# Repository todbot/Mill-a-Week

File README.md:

# Mill-a-Week
weekly experiments with othermachine Othermill by @todbot & @carlynorama

## Projects

### MyFirstOtherMillPendant - 22 May 2015
- Task: Use Illustrator to make a non-circuit design
- Notes:
  - Hard to align multiple SVGs

### LED-OtherCat - 29 May 2015
- Task: Make simple non-rectangular circuit in Eagle using 1/16" endmill
- Notes:
  - Can't do most through-hole with 1/16" --> Do extra hole pass at 1/32"

### HandCodedGerberPart01 - 5 Jun 2015
- Task: Explore how Otherplan imports Gerbers vs. SVGs, since in SVGs you can't do "put a hole here"
- Notes:
  - See [HandCodedGerberPart01/README.md](HandCodedGerberPart01/README.md)

### NeoJoints - 5 Jun 2015
- UPDATE: These have their own repo now: https://github.com/todbot/NeoJoints
- Task: Make "joints" for NeoPixel/WS2812 LED strip to make it easier to join pieces together
- Notes:
  - Programmatically generating these for different angles, LED spacing, etc. would be good.

### MillBug - 12 Jun 2015
- Task: Make an ATtiny85-based circuit using something other than LEDs
- Notes:
  - Soldering SMD on non-soldermask boards is a recipe for disaster if you have spazzy hands.
  - So, increase polygon "isolate" value for ground pour to give you
    bigger spacing to non-milled copper.

### OtherBlink - 3 Jul 2015 (originally Aug 2014)
- Task: See if Othermill can do SOIC & PLCC packages for ATtiny85 & WS2812, and make battery-powered flashing LED pendant with capsense touch sensor
- Notes:
  - capsense on battery-powered projects is challenging

### PlywoodPendant - 24 Jul 2015 
- Task: See if we can hit the independant plys in high-grade plywood
- Notes:
  - 
See if Othermill can do SOIC & PLCC packages for ATtiny85 & WS2812, and make battery-powered flashing LED pendant with capsense touch sensor
- Notes:
  - Lots of "chipout" around engraved areas. Would blue tape help?
  - We can make it thin enough for LEDs!

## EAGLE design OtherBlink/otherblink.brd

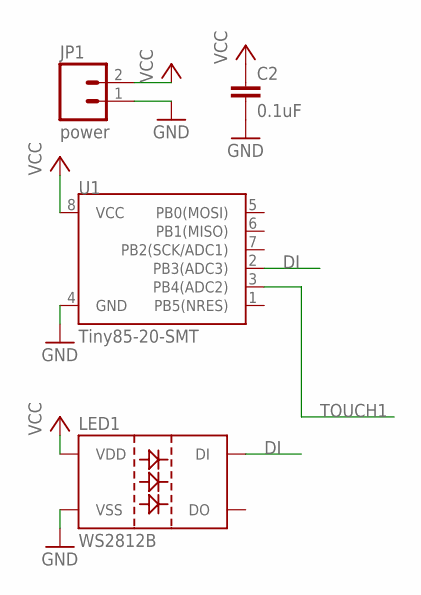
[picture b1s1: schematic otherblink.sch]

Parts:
C2: 0.1uF; 0603-CAP
JP1: power; 1X02_LONGPADS
LED1: WS2812B
U1: Tiny85-20-SMT; SO08-EIAJ

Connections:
DI: LED1.4 (DI), U1.2 (PB3(ADC3))
GND: C2.2, JP1.1, LED1.3 (VSS), U1.4 (GND)
TOUCH1: U1.3 (PB4(ADC2))
VCC: C2.1, JP1.2, LED1.1 (VDD), U1.8 (VCC)

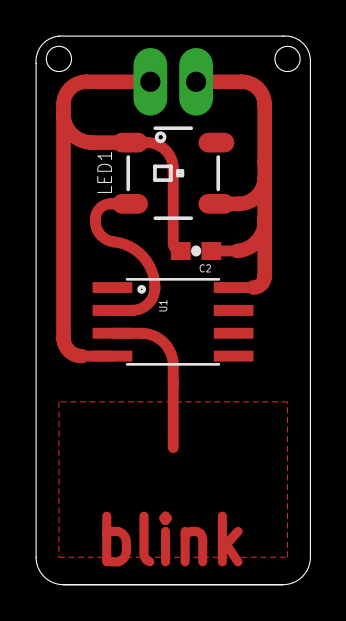
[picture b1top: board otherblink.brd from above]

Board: 2 copper layers, 15.2 x 30.5 mm, 4 parts (0 on the bottom side), 3 nets.

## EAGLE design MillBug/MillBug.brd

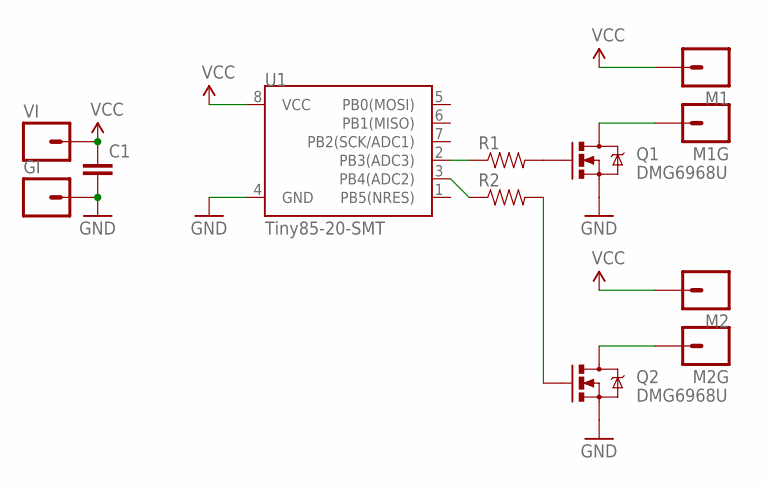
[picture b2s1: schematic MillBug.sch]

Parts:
C1: CAP0603-CAP; 0603-CAP
GI: M01PTH; 1X01
M1, M1G, M2, M2G: M01PTH; 1X01
Q1, Q2: DMG6968U; SOT23-3
R1, R2: RESISTOR0603-RES; 0603-RES
U1: Tiny85-20-SMT; SO08-EIAJ
VI: M01PTH; 1X01

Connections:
GND: C1.2, GI.1, Q1.2 (S), Q2.2 (S), U1.4 (GND)
unnamed: R2.1, U1.3 (PB4(ADC2))
unnamed: R1.1, U1.2 (PB3(ADC3))
unnamed: M1G.1, Q1.3 (D)
unnamed: Q1.1 (G), R1.2
unnamed: Q2.1 (G), R2.2
unnamed: M2G.1, Q2.3 (D)
VCC: C1.1, M1.1, M2.1, U1.8 (VCC), VI.1

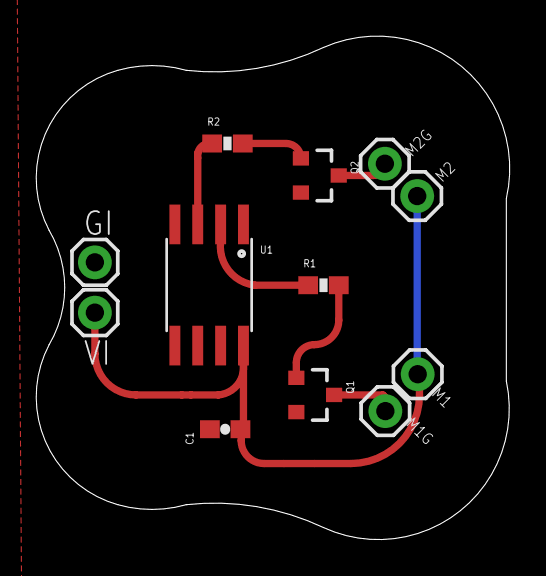
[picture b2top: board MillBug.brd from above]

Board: 2 copper layers, 26.3 x 28.0 mm, 12 parts (0 on the bottom side), 8 nets.

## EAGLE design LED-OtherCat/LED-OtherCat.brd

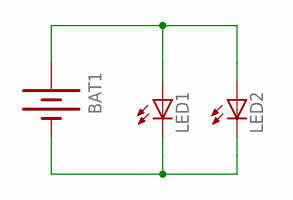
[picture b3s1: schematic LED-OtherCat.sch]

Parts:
BAT1: BATTERY20PTH; BATTCOM_20MM_PTH
LED1, LED2: LEDP-LCC-2-BACK; P-LCC-2-TOPLED-RG

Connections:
unnamed: BAT1.2 (-), LED1.C, LED2.C
unnamed: BAT1.1 (+), LED1.A, LED2.A

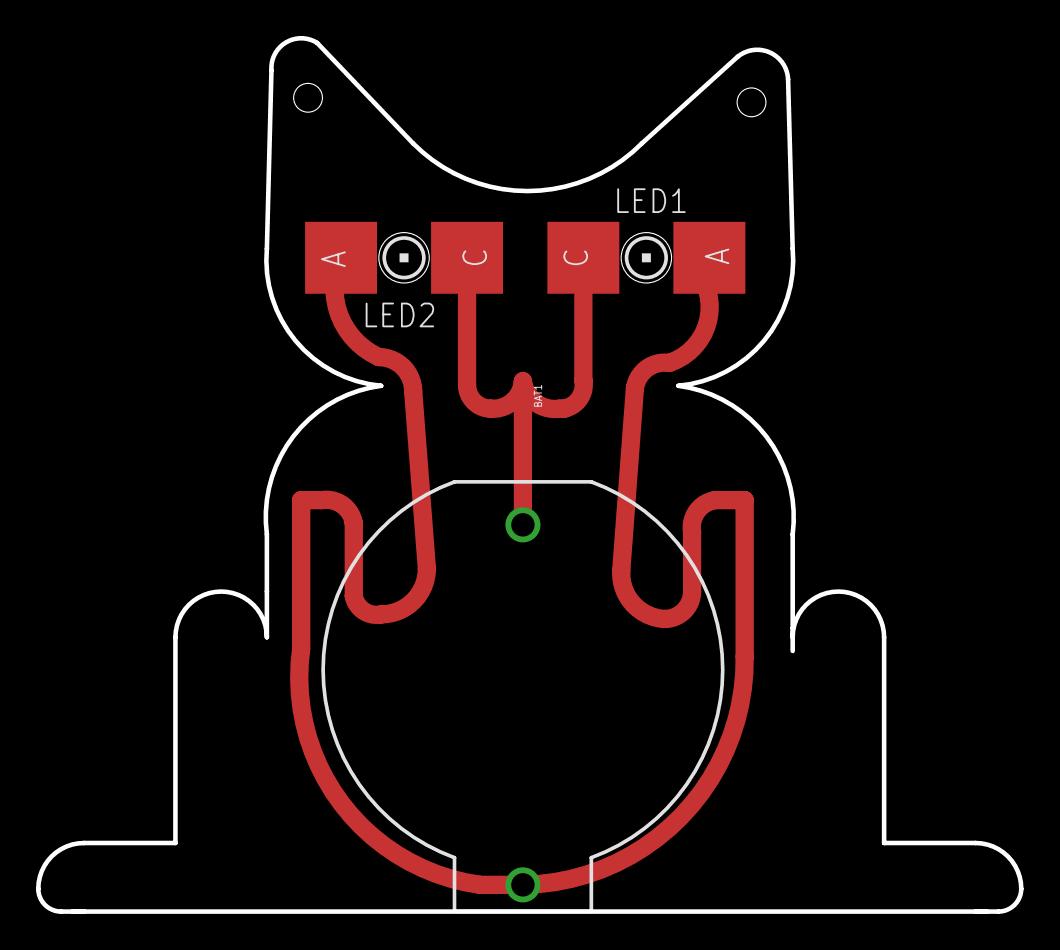
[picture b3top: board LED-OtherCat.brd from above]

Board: 2 copper layers, 54.6 x 48.5 mm, 3 parts (0 on the bottom side), 2 nets.

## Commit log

2015-05-30 added some readme
2015-05-30 added img refs
2015-05-30 added our handles
2015-06-05 Adding gerber file and readme
    finished gerber, started readme
2015-06-05 ulp, duh.
    ulp not uml
2015-06-06 Added link to image
2015-06-06 Added code annotations to README.md
2015-06-06 There were weird alignment issues on README.md
2015-06-06 added neojoints
2015-06-06 added experiments for 5 Jun to Readme
2015-06-08 cleaned up joints, now on v3; added possible jig (but it crashes otherplan)
2015-06-16 added millbug
2015-06-16 added millbug sch
2015-06-16 fixed readme date
2015-07-03 added otherblink
2015-07-03 updated readme to have otherblink info
2015-07-24 added PlywoodPendant
2015-09-02 added neojoint readme
2017-02-23 updated READMEs on new NeoJoints repo

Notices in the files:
parts and their libraries:
SparkFun-Electromechanical: Licensing: Creative Commons ShareAlike 4.0 International - https://creativecommons.org/licenses/by-sa/4.0
SparkFun-DigitalIC: Licensing: CC v3.0 Share-Alike You are welcome to use this library for commercial purposes.
